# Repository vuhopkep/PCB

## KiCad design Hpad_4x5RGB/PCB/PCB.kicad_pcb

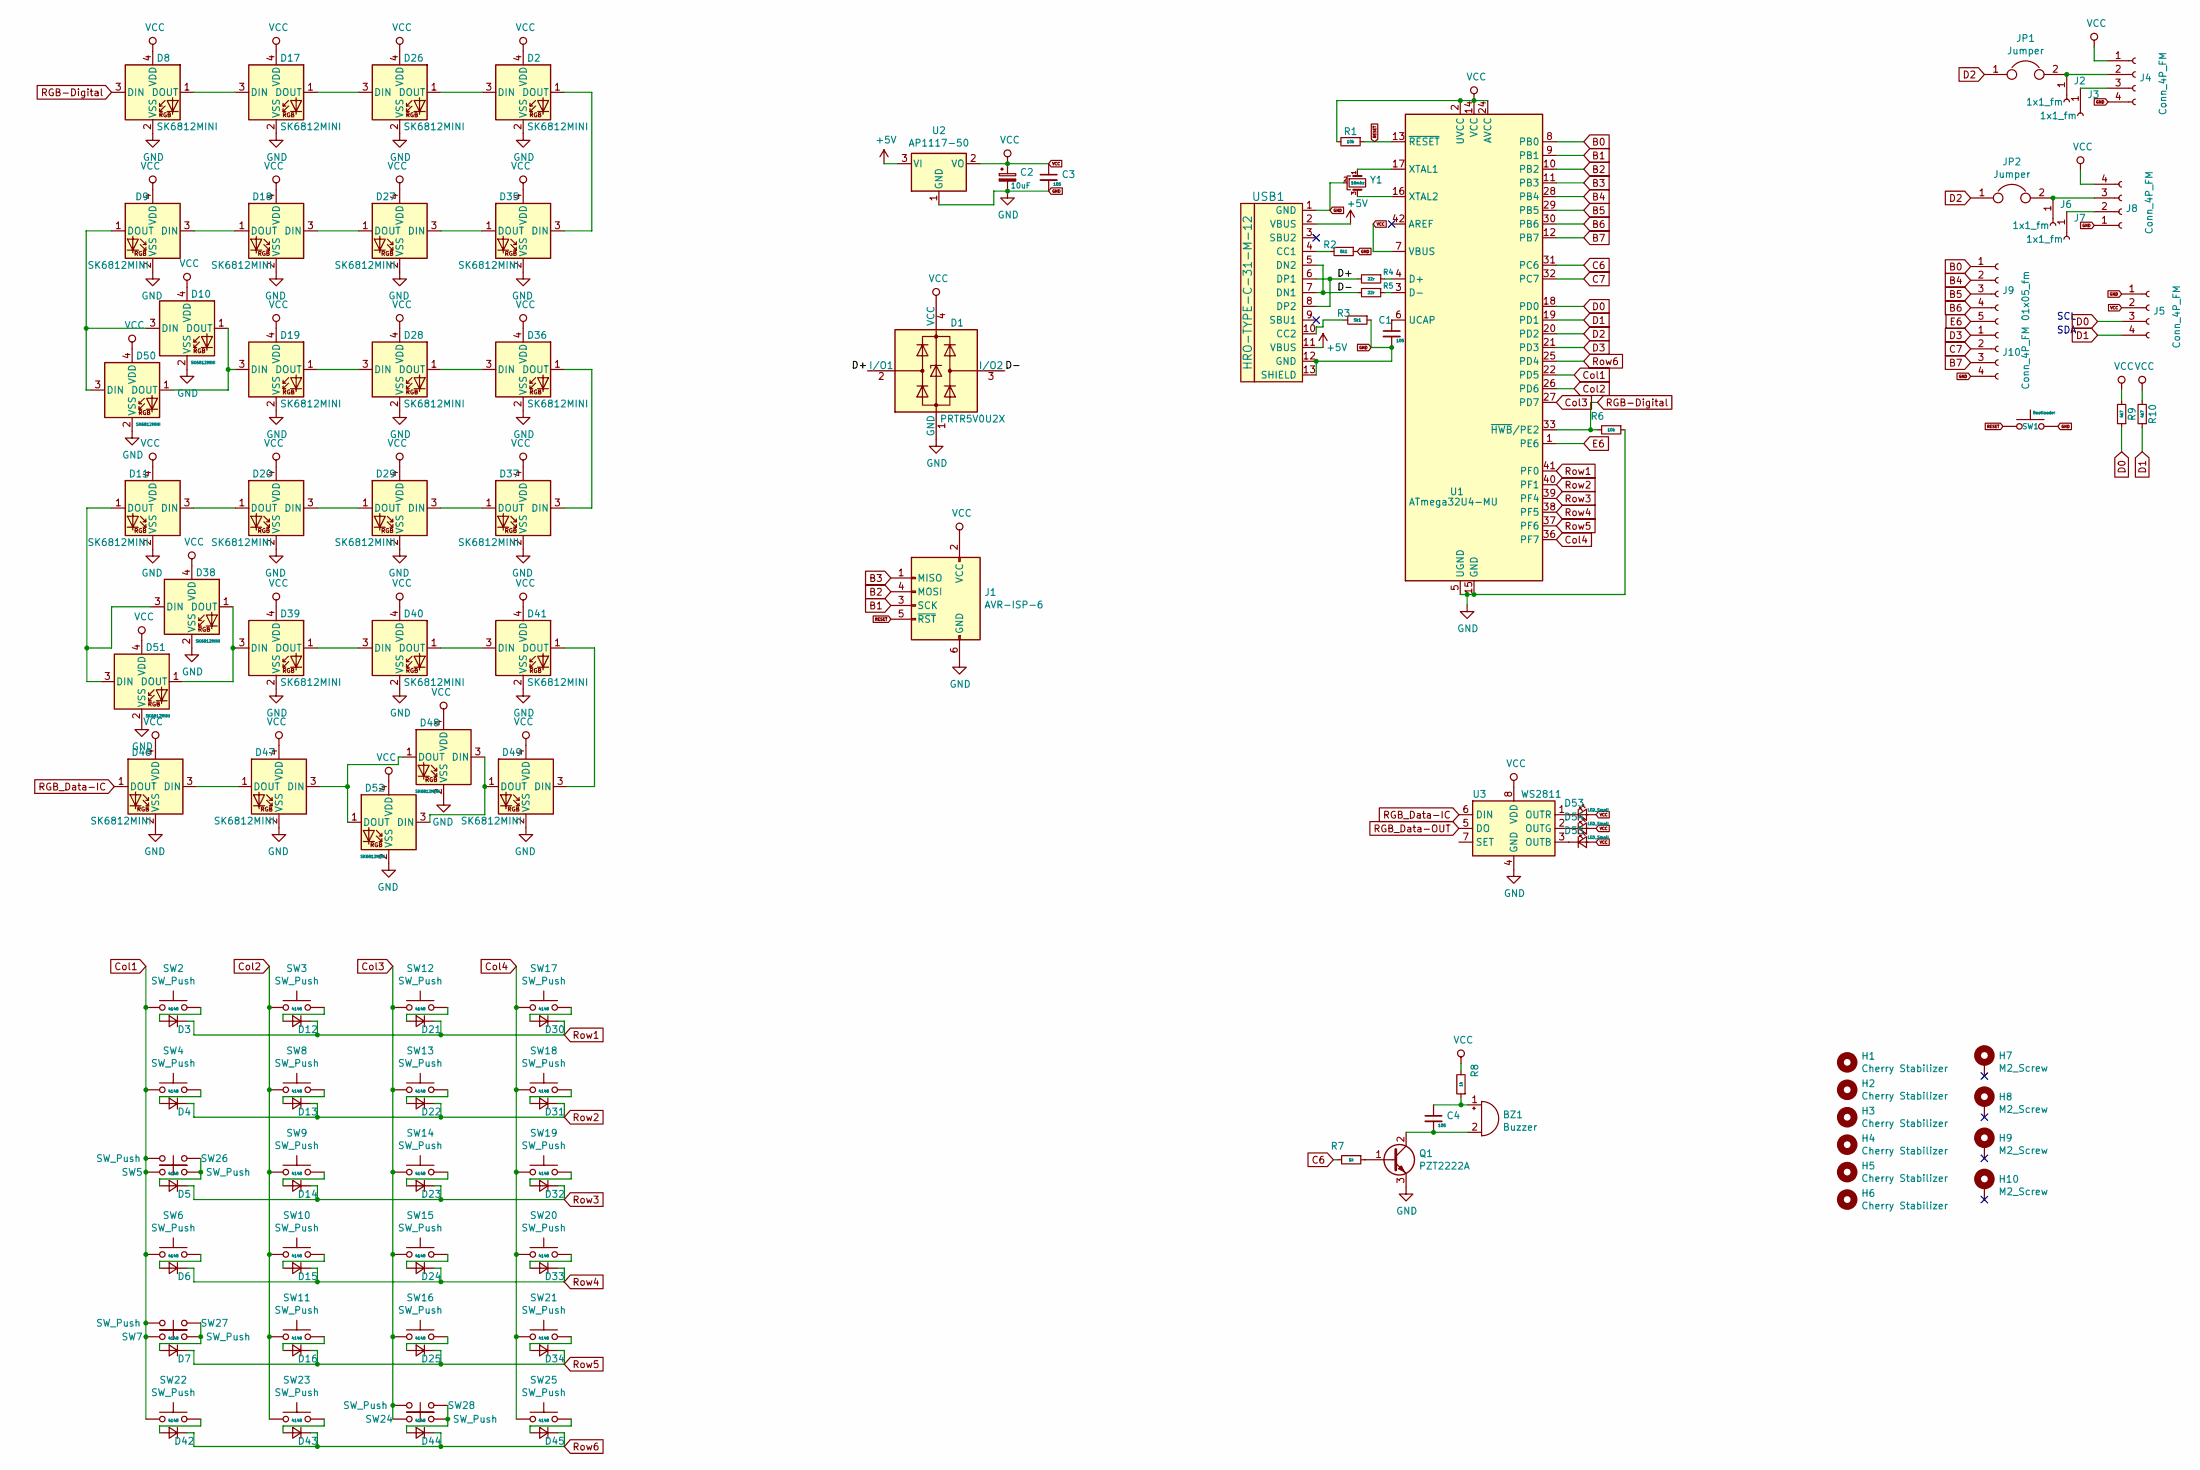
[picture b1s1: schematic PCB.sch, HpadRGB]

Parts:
BZ1: Buzzer; Buzzer_Murata_PKMCS0909E4000-R1
C1, C3, C4: 105; C_0805
C2: 10uF; CP_Tantalum_3216
D1: PRTR5V0U2X; SOT-143
D2, D8, D9, D10, D11, D17, D18, D19, D20, D26, D27, D28, D29, D35, D36, D37, D38, D39, D40, D41, D46, D47, D48, D49, D50, D51, D52: SK6812MINI; LED_SK6812-3535_Backlight
D3, D4, D5, D6, D7, D12, D13, D14, D15, D16, D21, D22, D23, D24, D25, D30, D31, D32, D33, D34, D42, D43, D44, D45: 4148; D_SOD-323_HandSoldering
D53, D54, D55: LED_Small; LED_0805_2012Metric
H1, H2, H3, H4, H5, H6: Cherry Stabilizer; Cherry_Stab_PCBMounted
H7, H8, H9, H10: M2_Screw; MountingHole_2.2mm_M2_Pad_Via
J1: AVR-ISP-6; AVR_ISP_6
J2, J3, J6, J7: 1x1_fm; PinHeader_1x01_P1.00mm_Vertical
J4, J8: Conn_4P_FM; HTP-CON-M411P
J5, J10: Conn_4P_FM; PinHeader_1x04_P2.54mm_Vertical
J9: 01x05_fm; PinSocket_1x05_P2.54mm_Vertical
JP1, JP2: Jumper; SolderJumper-2_P1.3mm_Open_RoundedPad1.0x1.5mm
Q1: PZT2222A; SOT-23W
R1, R6: 10k; R_0805_2012Metric
R2, R3: 5k1; R_0805_2012Metric
R4, R5: 22r; R_0805_2012Metric
R7, R8: 1k; R_0805_2012Metric
R9, R10: 4k7; R_0805_2012Metric
SW1: Bootloader; SW_SPST_B3U-1000P-B
SW2, SW3, SW4, SW5, SW6, SW7, SW8, SW9, SW10, SW11, SW12, SW13, SW14, SW15, SW16, SW17, SW18, SW19, SW20, SW21, SW22, SW23, SW24, SW25, SW26, SW27, SW28: SW_Push; CHERRY&ALPS_PCB_100H
U1: ATmega32U4-MU; QFN-44-1EP_7x7mm_P0.5mm_EP5.2x5.2mm
U2: AP1117-50; SOT-223-3_TabPin2
U3: WS2811; SOIC-8_3.9x4.9mm_P1.27mm
USB1: HRO-TYPE-C-31-M-12
Y1: 16mhz; Resonator_SMD_muRata_CSTxExxV-3Pin_3.0x1.1mm

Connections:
+5V: U2.3 (VI), USB1.2 (VBUS), USB1.11 (VBUS)
/D+: D1.2 (I/O1), R4.2, USB1.6 (DP1), USB1.8 (DP2)
/D-: D1.3 (I/O2), R5.2, USB1.5 (DN2), USB1.7 (DN1)
B0: J9.1, U1.8 (PB0)
B1: J1.3 (SCK), U1.9 (PB1)
B2: J1.4 (MOSI), U1.10 (PB2)
B3: J1.1 (MISO), U1.11 (PB3)
B4: J9.2, U1.28 (PB4)
B5: J9.3, U1.29 (PB5)
B6: J9.4, U1.30 (PB6)
B7: J10.3, U1.12 (PB7)
C6: R7.2, U1.31 (PC6)
C7: J10.2, U1.32 (PC7)
Col1: SW2.1, SW4.1, SW5.1, SW6.1, SW7.1, SW22.1, SW26.2, SW27.2, U1.22 (PD5)
Col2: SW3.1, SW8.1, SW9.1, SW10.1, SW11.1, SW23.1, U1.26 (PD6)
Col3: SW12.1, SW13.1, SW14.1, SW15.1, SW16.1, SW24.1, SW28.2, U1.27 (PD7)
Col4: SW17.1, SW18.1, SW19.1, SW20.1, SW21.1, SW25.1, U1.36 (PF7)
D0: J5.3, R9.1, U1.18 (PD0)
D1: J5.4, R10.1, U1.19 (PD1)
D2: JP1.1, JP2.1, U1.20 (PD2)
D3: J10.1, U1.21 (PD3)
E6: J9.5, U1.1 (PE6)
GND: C1.2, C2.2, C3.2, D1.1 (GND), D2.2 (VSS), D8.2 (VSS), D9.2 (VSS), D10.2 (VSS), D11.2 (VSS), D17.2 (VSS), D18.2 (VSS), D19.2 (VSS), D20.2 (VSS), D26.2 (VSS), D27.2 (VSS), D28.2 (VSS), D29.2 (VSS), D35.2 (VSS), D36.2 (VSS), D37.2 (VSS), D38.2 (VSS), D39.2 (VSS), D40.2 (VSS), D41.2 (VSS), D46.2 (VSS), D47.2 (VSS), D48.2 (VSS), D49.2 (VSS), D50.2 (VSS), D51.2 (VSS), D52.2 (VSS), J1.6 (GND), J4.4, J5.1, J8.1, J10.4, Q1.3 (E), R2.1, R3.1, R6.1, SW1.2, U1.5 (UGND), U1.15 (GND), U1.23 (GND), U1.35 (GND), U1.43 (GND), U1.45 (GND), U2.1 (GND), U3.4 (GND), USB1.1 (GND), USB1.12 (GND), USB1.13 (SHIELD), Y1.2; also elsewhere on the board
unnamed: BZ1.1 (-), C4.1, R8.1
unnamed: BZ1.2 (+), C4.2, Q1.2 (C)
unnamed: C1.1, U1.6 (UCAP)
unnamed: D2.1 (DOUT), D35.3 (DIN)
unnamed: D2.3 (DIN), D26.1 (DOUT)
unnamed: D3.2 (A), SW2.2
unnamed: D4.2 (A), SW4.2
unnamed: D5.2 (A), SW5.2, SW26.1
unnamed: D6.2 (A), SW6.2
unnamed: D7.2 (A), SW7.2, SW27.1
unnamed: D10.1 (DOUT), D19.3 (DIN), D50.1 (DOUT)
unnamed: D9.1 (DOUT), D10.3 (DIN), D50.3 (DIN)
unnamed: D11.1 (DOUT), D38.3 (DIN), D51.3 (DIN)
unnamed: D11.3 (DIN), D20.1 (DOUT)
unnamed: D12.2 (A), SW3.2
unnamed: D13.2 (A), SW8.2
unnamed: D14.2 (A), SW9.2
unnamed: D15.2 (A), SW10.2
unnamed: D16.2 (A), SW11.2
unnamed: D17.1 (DOUT), D26.3 (DIN)
unnamed: D8.1 (DOUT), D17.3 (DIN)
unnamed: D9.3 (DIN), D18.1 (DOUT)
unnamed: D18.3 (DIN), D27.1 (DOUT)
unnamed: D19.1 (DOUT), D28.3 (DIN)
unnamed: D20.3 (DIN), D29.1 (DOUT)
unnamed: D21.2 (A), SW12.2
unnamed: D22.2 (A), SW13.2
unnamed: D23.2 (A), SW14.2
unnamed: D24.2 (A), SW15.2
unnamed: D25.2 (A), SW16.2
unnamed: D27.3 (DIN), D35.1 (DOUT)
unnamed: D28.1 (DOUT), D36.3 (DIN)
unnamed: D29.3 (DIN), D37.1 (DOUT)
unnamed: D30.2 (A), SW17.2
unnamed: D31.2 (A), SW18.2
unnamed: D32.2 (A), SW19.2
unnamed: D33.2 (A), SW20.2
unnamed: D34.2 (A), SW21.2
unnamed: D36.1 (DOUT), D37.3 (DIN)
unnamed: D38.1 (DOUT), D39.3 (DIN), D51.1 (DOUT)
unnamed: D39.1 (DOUT), D40.3 (DIN)
unnamed: D40.1 (DOUT), D41.3 (DIN)
unnamed: D41.1 (DOUT), D49.3 (DIN)
unnamed: D42.2 (A), SW22.2
unnamed: D43.2 (A), SW23.2
unnamed: D44.2 (A), SW24.2, SW28.1
unnamed: D45.2 (A), SW25.2
unnamed: D46.3 (DIN), D47.1 (DOUT)
unnamed: D47.3 (DIN), D48.1 (DOUT), D52.1 (DOUT)
unnamed: D48.3 (DIN), D49.1 (DOUT), D52.3 (DIN)
unnamed: D53.1 (K), U3.1 (OUTR)
unnamed: D54.1 (K), U3.2 (OUTG)
unnamed: D55.1 (K), U3.3 (OUTB)
unnamed: J2.1, J4.2, JP1.2
unnamed: J3.1, J4.3
unnamed: J6.1, J8.3, JP2.2
unnamed: J7.1, J8.2
unnamed: Q1.1 (B), R7.1
unnamed: R2.2, USB1.4 (CC1)
unnamed: R3.2, USB1.10 (CC2)
unnamed: R4.1, U1.4 (D+)
unnamed: R5.1, U1.3 (D-)
unnamed: U1.16 (XTAL2), Y1.3
unnamed: U1.17 (XTAL1), Y1.1
RESET: J1.5 (~RST), R1.1, SW1.1, U1.13 (~RESET); also elsewhere on the board
RGB-Digital: D8.3 (DIN), R6.2, U1.33 (~HWB~/PE2)
RGB_Data-IC: D46.1 (DOUT), U3.6 (DIN)
RGB_Data-OUT: U3.5 (DO)
Row1: D3.1 (K), D12.1 (K), D21.1 (K), D30.1 (K), U1.41 (PF0)
Row2: D4.1 (K), D13.1 (K), D22.1 (K), D31.1 (K), U1.40 (PF1)
Row3: D5.1 (K), D14.1 (K), D23.1 (K), D32.1 (K), U1.39 (PF4)
Row4: D6.1 (K), D15.1 (K), D24.1 (K), D33.1 (K), U1.38 (PF5)
Row5: D7.1 (K), D16.1 (K), D25.1 (K), D34.1 (K), U1.37 (PF6)
Row6: D42.1 (K), D43.1 (K), D44.1 (K), D45.1 (K), U1.25 (PD4)
VCC: C2.1, C3.1, D1.4 (VCC), D2.4 (VDD), D8.4 (VDD), D9.4 (VDD), D10.4 (VDD), D11.4 (VDD), D17.4 (VDD), D18.4 (VDD), D19.4 (VDD), D20.4 (VDD), D26.4 (VDD), D27.4 (VDD), D28.4 (VDD), D29.4 (VDD), D35.4 (VDD), D36.4 (VDD), D37.4 (VDD), D38.4 (VDD), D39.4 (VDD), D40.4 (VDD), D41.4 (VDD), D46.4 (VDD), D47.4 (VDD), D48.4 (VDD), D49.4 (VDD), D50.4 (VDD), D51.4 (VDD), D52.4 (VDD), D53.2 (A), D54.2 (A), D55.2 (A), J1.2 (VCC), J4.1, J5.2, J8.4, R1.2, R8.2, R9.2, R10.2, U1.2 (UVCC), U1.7 (VBUS), U1.14 (VCC), U1.24 (AVCC), U1.34 (VCC), U1.44 (AVCC), U2.2 (VO), U3.8 (VDD)

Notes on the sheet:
SCL
SDA

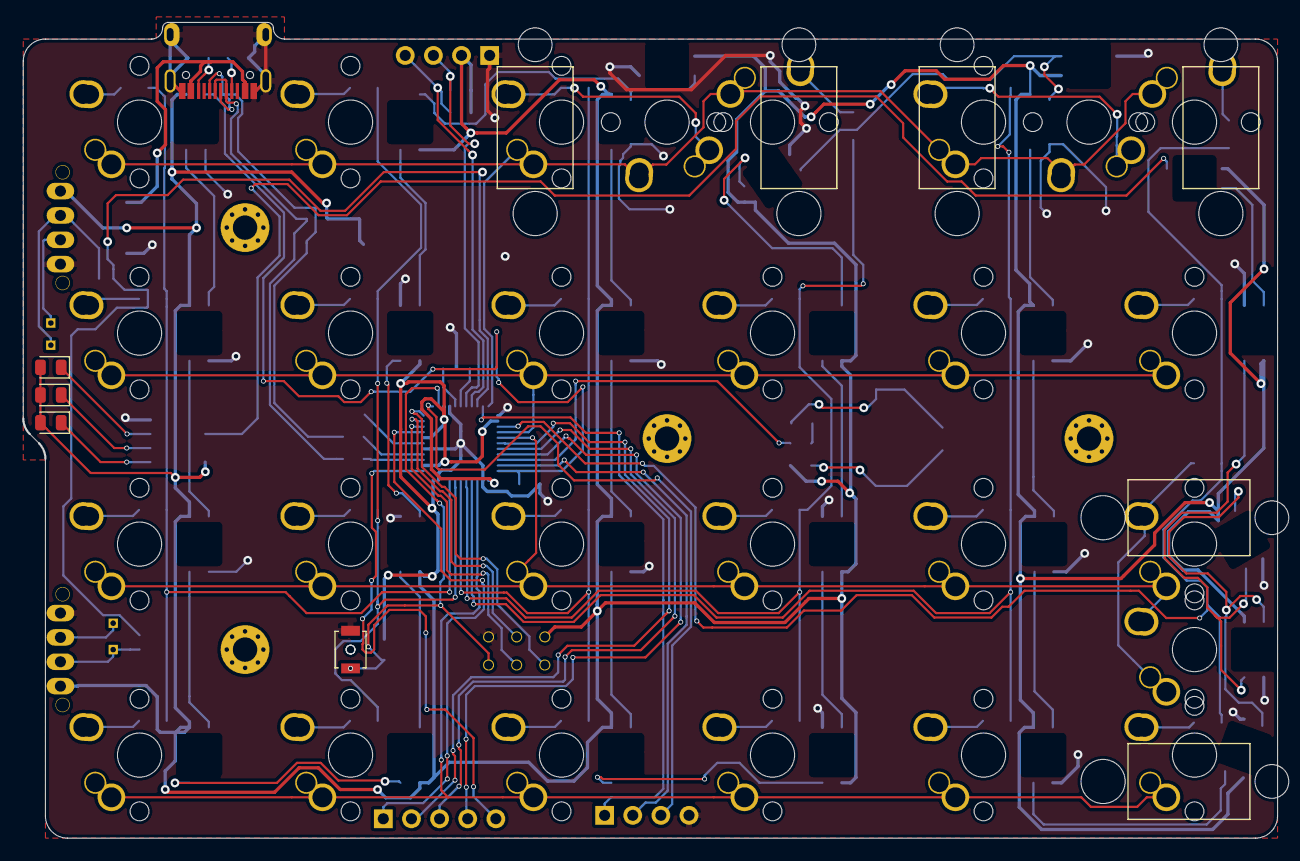
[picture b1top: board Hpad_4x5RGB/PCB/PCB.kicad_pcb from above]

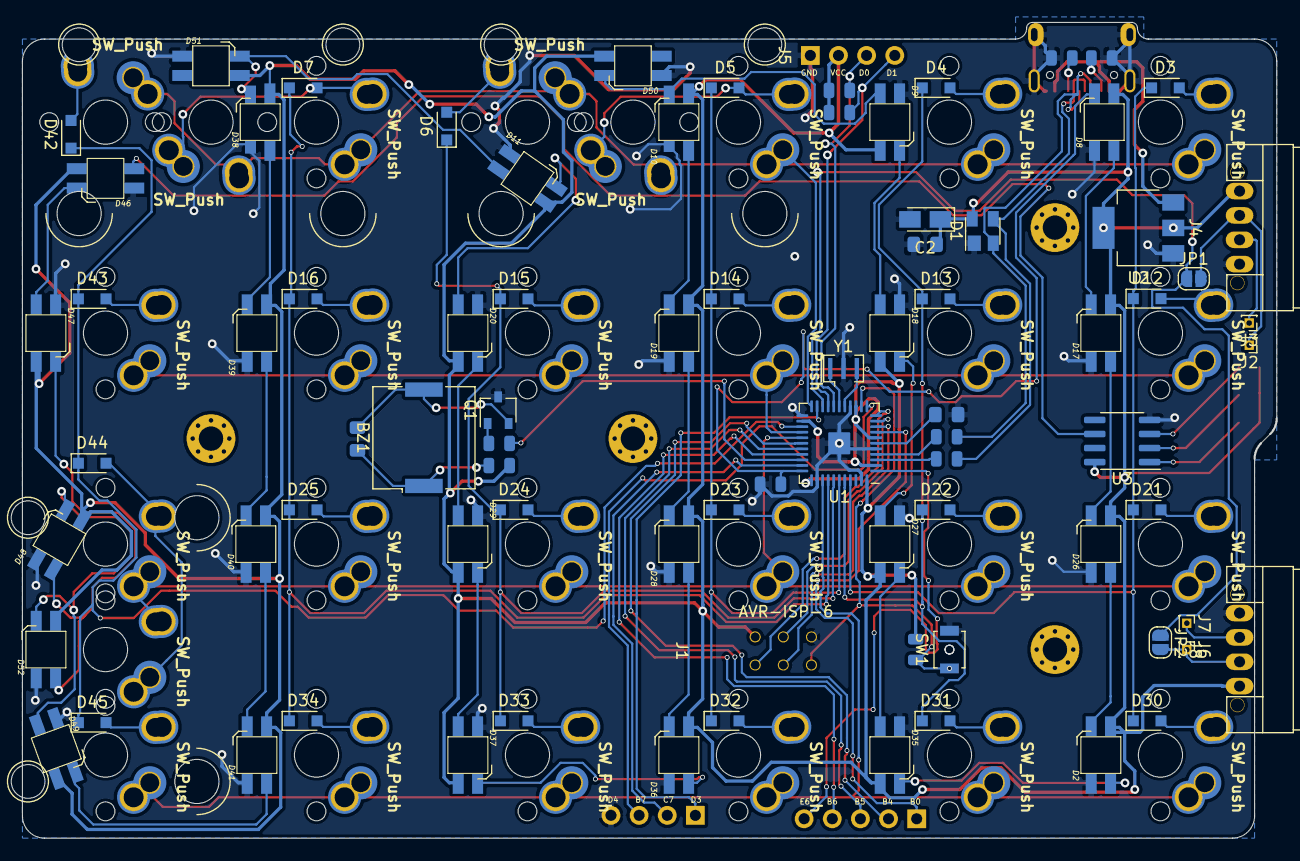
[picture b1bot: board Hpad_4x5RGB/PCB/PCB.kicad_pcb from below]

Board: 2 copper layers, 113.2 x 73.7 mm, 127 parts (83 on the bottom side), 97 nets.

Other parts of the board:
SW1#2: Bootloader; SW_SPST_B3U-1000P-B

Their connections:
GND: SW1#2.2; also elsewhere on the board
RESET: SW1#2.1; also elsewhere on the board

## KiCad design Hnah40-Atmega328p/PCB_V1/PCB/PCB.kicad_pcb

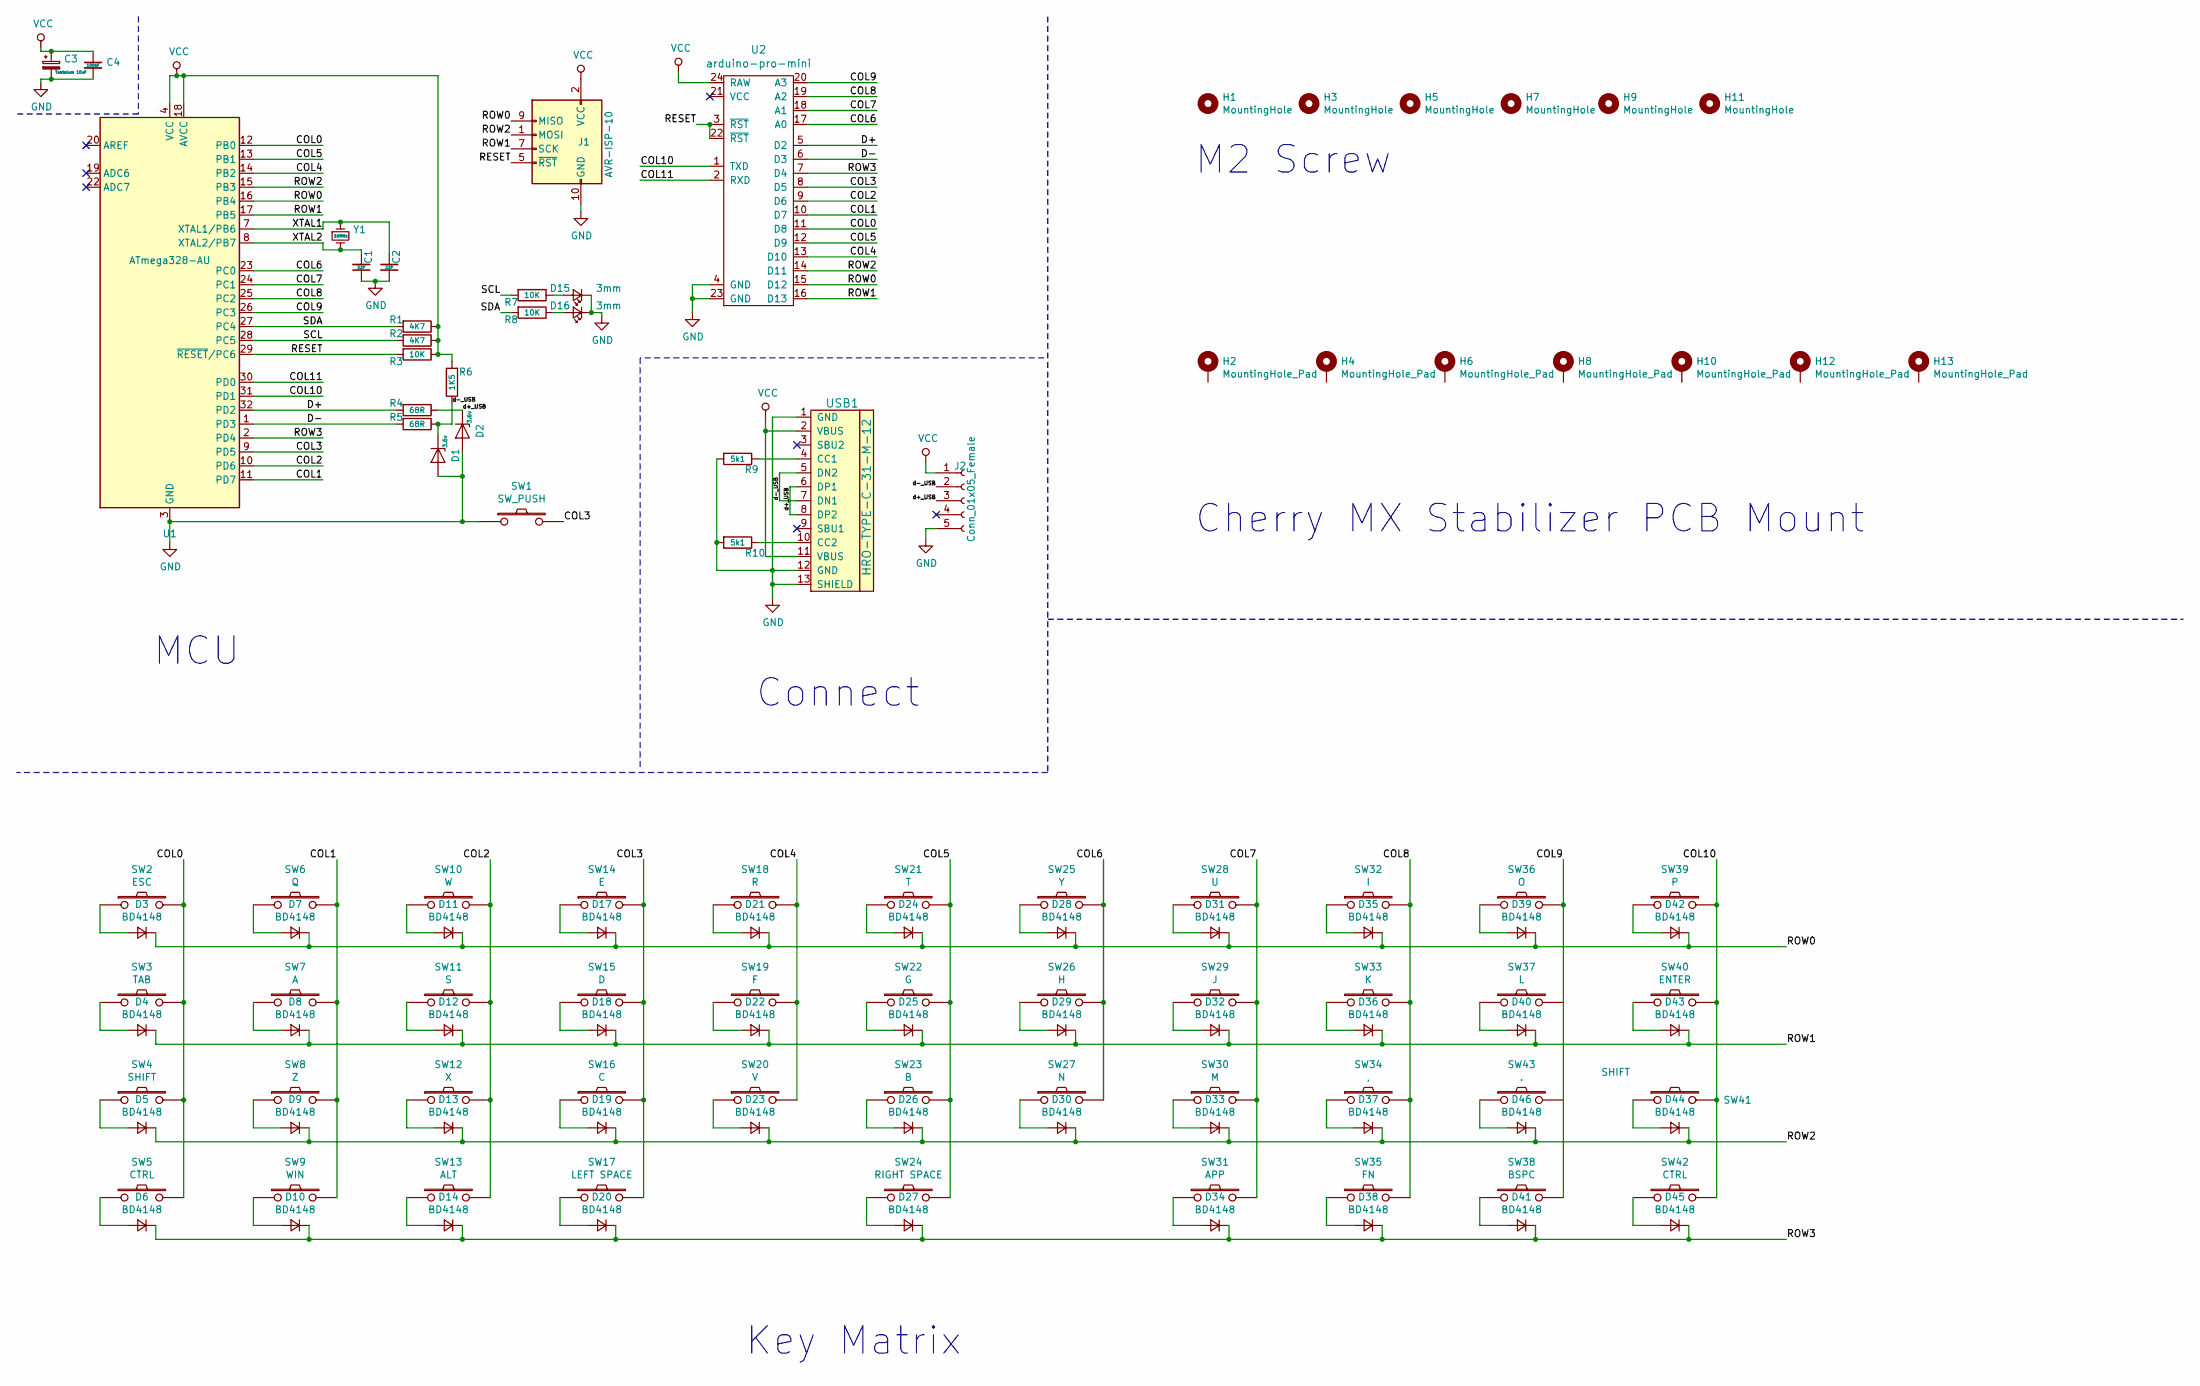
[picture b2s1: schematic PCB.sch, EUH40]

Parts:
C1, C2: 22P; C_0805_2012Metric
C3: Tantalum 10uF; CP_Tantalum_3216
C4: 100nF; C_0805_2012Metric
D1, D2: 3.6v; D_SOD-123
D3, D4, D5, D6, D7, D8, D9, D10, D11, D12, D13, D14, D17, D18, D19, D20, D21, D22, D23, D24, D25, D26, D27, D28, D29, D30, D31, D32, D33, D34, D35, D36, D37, D38, D39, D40, D41, D42, D43, D44, D45, D46: BD4148; D_0805_Mab_ideal
D15, D16: 3mm
H1, H3, H5, H7, H9, H11: MountingHole; Cherry_Stab_PCBMounted
H2, H4, H6, H8, H10, H12, H13: MountingHole_Pad; Poker_oval_hole
J1: AVR-ISP-10; AVR_ICSP_5x2
J2: Conn_01x05_Female; PinHeader_1x05_P2.54mm_Vertical
R1, R2: 4K7; R_0805_2012Metric
R3, R7, R8: 10K; R_0805_2012Metric
R4, R5: 68R; R_0805_2012Metric
R6: 1K5; R_0805_2012Metric
R9, R10: 5k1; R_0805_2012Metric
SW1: SW_PUSH; Nidec_Copal_SH-7010A
SW2: ESC; CHERRY_PCB_100H
SW3: TAB; CHERRY_PCB_100H
SW4: SHIFT; CHERRY_PCB_100H
SW5, SW42: CTRL; CHERRY_PCB_100H
SW6: Q; CHERRY_PCB_100H
SW7: A; CHERRY_PCB_100H
SW8: Z; CHERRY_PCB_100H
SW9: WIN; CHERRY_PCB_100H
SW10: W; CHERRY_PCB_100H
SW11: S; CHERRY_PCB_100H
SW12: X; CHERRY_PCB_100H
SW13: ALT; CHERRY_PCB_100H
SW14: E; CHERRY_PCB_100H
SW15: D; CHERRY_PCB_100H
SW16: C; CHERRY_PCB_100H
SW17: LEFT SPACE; CHERRY_PCB_100H
SW18: R; CHERRY_PCB_100H
SW19: F; CHERRY_PCB_100H
SW20: V; CHERRY_PCB_100H
SW21: T; CHERRY_PCB_100H
SW22: G; CHERRY_PCB_100H
SW23: B; CHERRY_PCB_100H
SW24: RIGHT SPACE; CHERRY_PCB_100H
SW25: Y; CHERRY_PCB_100H
SW26: H; CHERRY_PCB_100H
SW27: N; CHERRY_PCB_100H
SW28: U; CHERRY_PCB_100H
SW29: J; CHERRY_PCB_100H
SW30: M; CHERRY_PCB_100H
SW31: APP; CHERRY_PCB_100H
SW32: I; CHERRY_PCB_100H
SW33: K; CHERRY_PCB_100H
SW34: ,; CHERRY_PCB_100H
SW35: FN; CHERRY_PCB_100H
SW36: O; CHERRY_PCB_100H
SW37: L; CHERRY_PCB_100H
SW38: BSPC; CHERRY_PCB_100H
SW39: P; CHERRY_PCB_100H
SW40: ENTER; CHERRY_PCB_100H
SW41: SHIFT; CherryMX_Shift
SW43: .; CHERRY_PCB_100H
U1: ATmega328-AU; TQFP-32_7x7mm_P0.8mm
U2: arduino-pro-mini; Pro_mini
USB1: HRO-TYPE-C-31-M-12
Y1: 16MHz; Crystal_SMD_5032

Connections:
/COL0: SW2.2, SW3.2, SW4.2, SW5.2, U1.12 (PB0), U2.11 (D8)
/COL1: SW6.2, SW7.2, SW8.2, SW9.2, U1.11 (PD7), U2.10 (D7)
/COL2: SW10.2, SW11.2, SW12.2, SW13.2, U1.10 (PD6), U2.9 (D6)
/COL3: SW1.2, SW14.2, SW15.2, SW16.2, SW17.2, U1.9 (PD5), U2.8 (D5)
/COL4: SW18.2, SW19.2, SW20.2, U1.14 (PB2), U2.13 (D10)
/COL5: SW21.2, SW22.2, SW23.2, SW24.2, U1.13 (PB1), U2.12 (D9)
/COL6: SW25.2, SW26.2, SW27.2, U1.23 (PC0), U2.17 (A0)
/COL7: SW28.2, SW29.2, SW30.2, SW31.2, U1.24 (PC1), U2.18 (A1)
/COL8: SW32.2, SW33.2, SW34.2, SW35.2, U1.25 (PC2), U2.19 (A2)
/COL9: SW36.2, SW37.2, SW38.2, SW43.2, U1.26 (PC3), U2.20 (A3)
/COL10: SW39.2, SW40.2, SW41.2, SW42.2, U1.31 (PD1), U2.1 (TXD)
/COL11: U1.30 (PD0), U2.2 (RXD)
/D+: R4.2, U1.32 (PD2), U2.5 (D2)
/D-: R5.2, U1.1 (PD3), U2.6 (D3)
/RESET: J1.5 (~RST), R3.2, U1.29 (~RESET~/PC6), U2.3 (~RST), U2.22 (~RST)
/ROW0: D3.1 (K), D7.1 (K), D11.1 (K), D17.1 (K), D21.1 (K), D24.1 (K), D28.1 (K), D31.1 (K), D35.1 (K), D39.1 (K), D42.1 (K), J1.9 (MISO), U1.16 (PB4), U2.15 (D12)
/ROW1: D4.1 (K), D8.1 (K), D12.1 (K), D18.1 (K), D22.1 (K), D25.1 (K), D29.1 (K), D32.1 (K), D36.1 (K), D40.1 (K), D43.1 (K), J1.7 (SCK), U1.17 (PB5), U2.16 (D13)
/ROW2: D5.1 (K), D9.1 (K), D13.1 (K), D19.1 (K), D23.1 (K), D26.1 (K), D30.1 (K), D33.1 (K), D37.1 (K), D44.1 (K), D46.1 (K), J1.1 (MOSI), U1.15 (PB3), U2.14 (D11)
/ROW3: D6.1 (K), D10.1 (K), D14.1 (K), D20.1 (K), D27.1 (K), D34.1 (K), D38.1 (K), D41.1 (K), D45.1 (K), U1.2 (PD4), U2.7 (D4)
/SCL: R2.2, R7.2, U1.28 (PC5)
/SDA: R1.2, R8.2, U1.27 (PC4)
/XTAL1: C2.2, U1.7 (XTAL1/PB6), Y1.1
/XTAL2: C1.2, U1.8 (XTAL2/PB7), Y1.2
/d+_USB: D2.1 (K), J2.3, R4.1, USB1.6 (DP1), USB1.8 (DP2)
/d-_USB: D1.1 (K), J2.2, R5.1, R6.1, USB1.5 (DN2), USB1.7 (DN1)
GND: C1.1, C2.1, C3.2, C4.2, D1.2 (A), D2.2 (A), D15.1 (K), D16.1 (K), J1.4 (GND), J1.6 (GND), J1.8 (GND), J1.10 (GND), J2.5, R9.2, R10.2, SW1.1, U1.3 (GND), U1.5 (GND), U1.21 (GND), U2.4 (GND), U2.23 (GND), USB1.1 (GND), USB1.12 (GND), USB1.13 (SHIELD)
unnamed: D3.2 (A), SW2.1
unnamed: D4.2 (A), SW3.1
unnamed: D5.2 (A), SW4.1
unnamed: D6.2 (A), SW5.1
unnamed: D7.2 (A), SW6.1
unnamed: D8.2 (A), SW7.1
unnamed: D9.2 (A), SW8.1
unnamed: D10.2 (A), SW9.1
unnamed: D11.2 (A), SW10.1
unnamed: D12.2 (A), SW11.1
unnamed: D13.2 (A), SW12.1
unnamed: D14.2 (A), SW13.1
unnamed: D15.2 (A), R7.1
unnamed: D16.2 (A), R8.1
unnamed: D17.2 (A), SW14.1
unnamed: D18.2 (A), SW15.1
unnamed: D19.2 (A), SW16.1
unnamed: D20.2 (A), SW17.1
unnamed: D21.2 (A), SW18.1
unnamed: D22.2 (A), SW19.1
unnamed: D23.2 (A), SW20.1
unnamed: D24.2 (A), SW21.1
unnamed: D25.2 (A), SW22.1
unnamed: D26.2 (A), SW23.1
unnamed: D27.2 (A), SW24.1
unnamed: D28.2 (A), SW25.1
unnamed: D29.2 (A), SW26.1
unnamed: D30.2 (A), SW27.1
unnamed: D31.2 (A), SW28.1
unnamed: D32.2 (A), SW29.1
unnamed: D33.2 (A), SW30.1
unnamed: D34.2 (A), SW31.1
unnamed: D35.2 (A), SW32.1
unnamed: D36.2 (A), SW33.1
unnamed: D37.2 (A), SW34.1
unnamed: D38.2 (A), SW35.1
unnamed: D39.2 (A), SW36.1
unnamed: D40.2 (A), SW37.1
unnamed: D41.2 (A), SW38.1
unnamed: D42.2 (A), SW39.1
unnamed: D43.2 (A), SW40.1
unnamed: D44.2 (A), SW41.1
unnamed: D45.2 (A), SW42.1
unnamed: D46.2 (A), SW43.1
unnamed: R9.1, USB1.4 (CC1)
unnamed: R10.1, USB1.10 (CC2)
VCC: C3.1, C4.1, J1.2 (VCC), J2.1, R1.1, R2.1, R3.1, R6.2, U1.4 (VCC), U1.6 (VCC), U1.18 (AVCC), U2.24 (RAW), USB1.2 (VBUS), USB1.11 (VBUS)

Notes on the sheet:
M2 Screw
Cherry MX Stabilizer PCB Mount
MCU
Connect
Key Matrix

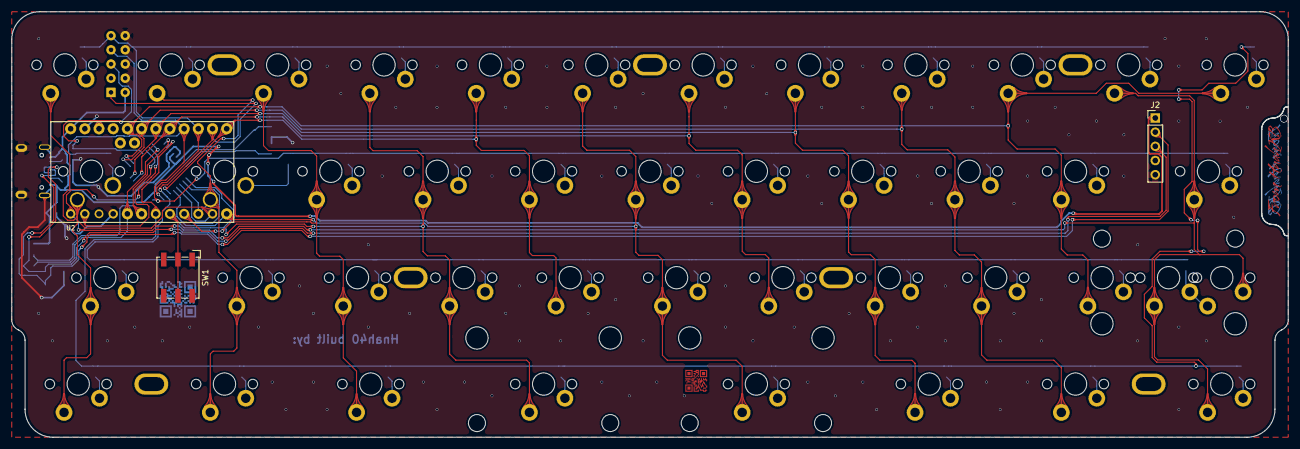
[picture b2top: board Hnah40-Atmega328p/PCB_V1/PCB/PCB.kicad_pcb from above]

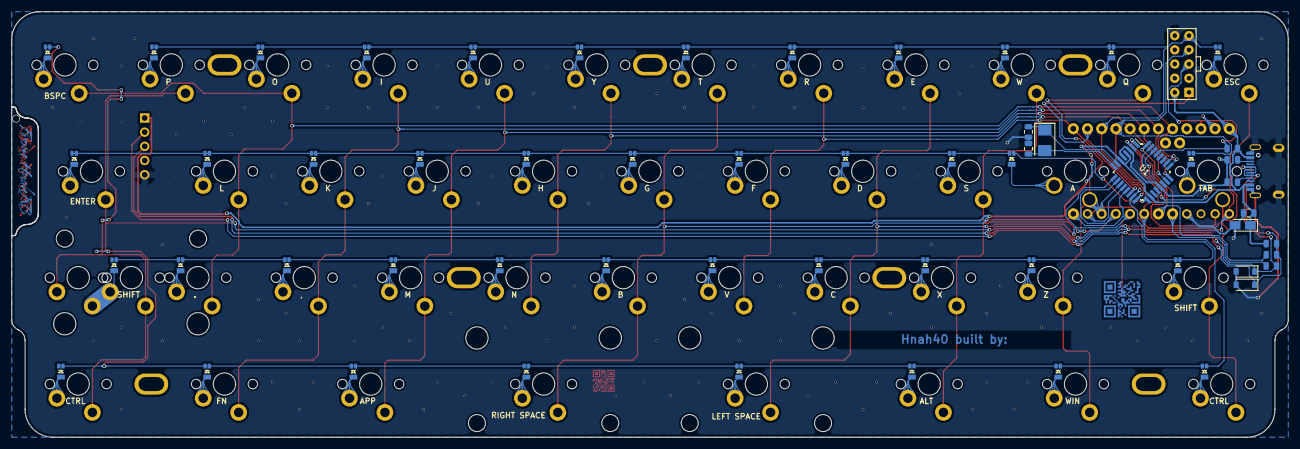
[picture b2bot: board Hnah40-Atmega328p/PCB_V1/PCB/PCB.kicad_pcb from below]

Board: 2 copper layers, 228.6 x 76.2 mm, 116 parts (58 on the bottom side), 69 nets.

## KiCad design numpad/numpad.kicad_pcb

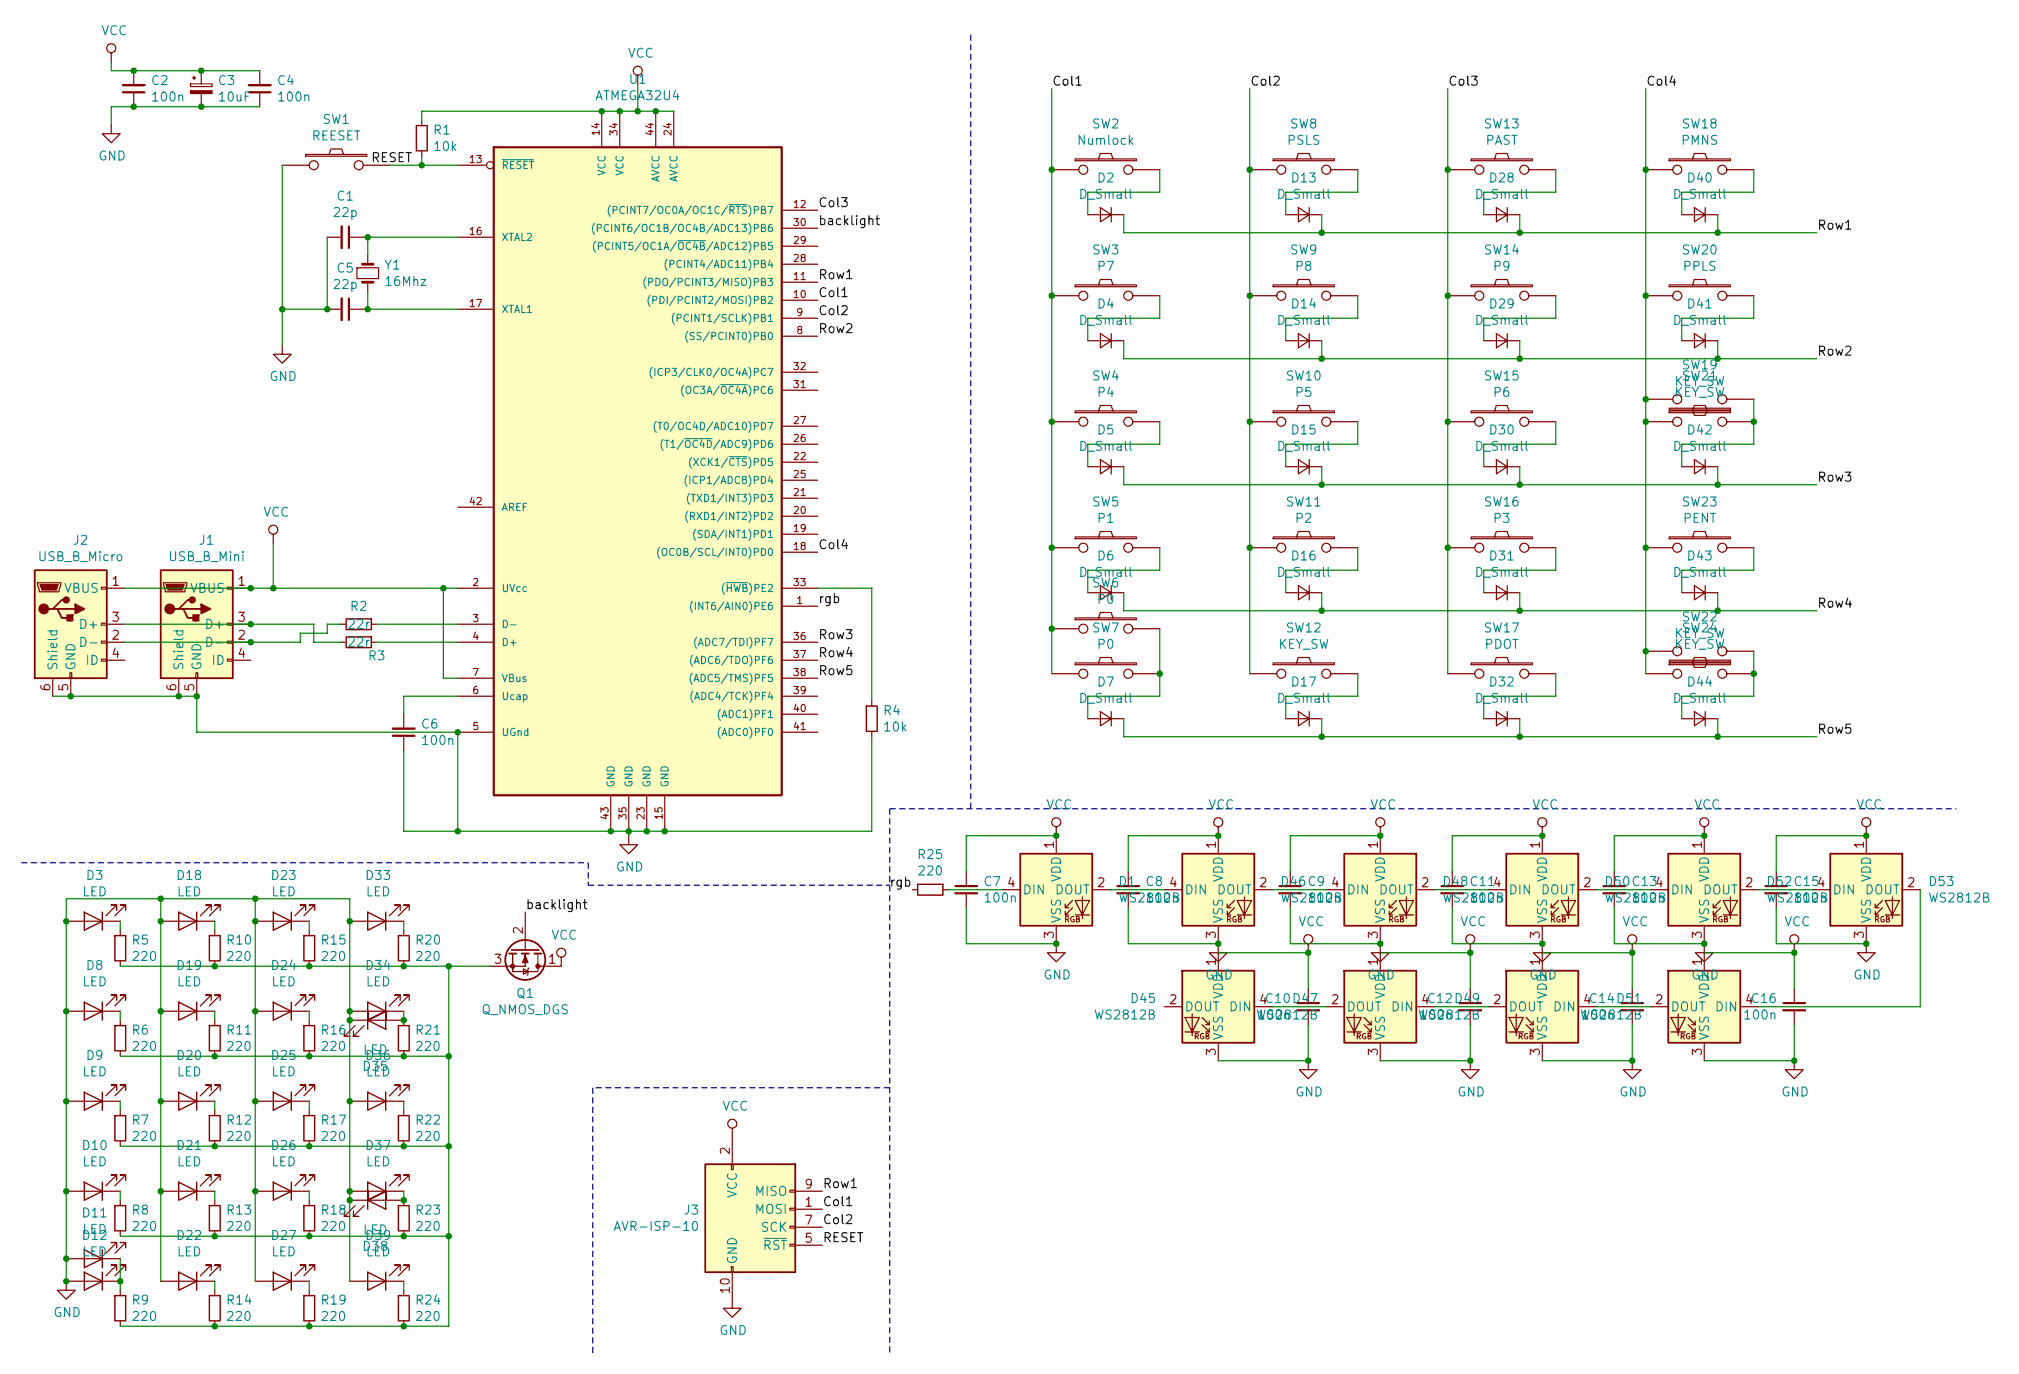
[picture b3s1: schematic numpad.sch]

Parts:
C1, C5: 22p; C_0805
C2, C4, C6, C7, C8, C9, C10, C11, C12, C13, C14, C15, C16: 100n; C_0805
C3: 10uF; CP_Tantalum_3216
D1, D45, D46, D47, D48, D49, D50, D51, D52, D53: WS2812B; LED_WS2812B_PLCC4_5.0x5.0mm_P3.2mm
D2, D4, D5, D6, D7, D13, D14, D15, D16, D17, D28, D29, D30, D31, D32, D40, D41, D42, D43, D44: D_Small; D_0805
D3, D8, D9, D10, D11, D12, D18, D19, D20, D21, D22, D23, D24, D25, D26, D27, D33, D34, D35, D36, D37, D38, D39: LED; CHERRY_MX_LED_3MM
J1: USB_B_Mini; USB_MINI_MAB
J2: USB_B_Micro; USB_Micro
J3: AVR-ISP-10; AVR_ICSP_5x2
Q1: Q_NMOS_DGS; SOT-23
R1, R4: 10k; R_0805
R2, R3: 22r; R_0805
R5, R6, R7, R8, R9, R10, R11, R12, R13, R14, R15, R16, R17, R18, R19, R20, R21, R22, R23, R24, R25: 220; R_0805
SW1: REESET; SW_SPST_TL3342
SW2: Numlock; CHERRY_PCB_100H
SW3: P7; CHERRY_PCB_100H
SW4: P4; CHERRY_PCB_100H
SW5: P1; CHERRY_PCB_100H
SW6, SW7: P0; CHERRY_PCB_100H
SW8: PSLS; CHERRY_PCB_100H
SW9: P8; CHERRY_PCB_100H
SW10: P5; CHERRY_PCB_100H
SW11: P2; CHERRY_PCB_100H
SW12, SW19, SW21, SW22, SW24: KEY_SW; CHERRY_PCB_100H
SW13: PAST; CHERRY_PCB_100H
SW14: P9; CHERRY_PCB_100H
SW15: P6; CHERRY_PCB_100H
SW16: P3; CHERRY_PCB_100H
SW17: PDOT; CHERRY_PCB_100H
SW18: PMNS; CHERRY_PCB_100H
SW20: PPLS; CHERRY_PCB_100H
SW23: PENT; CHERRY_PCB_100H
U1: ATMEGA32U4; TQFP-44_Pitch0.8mm
Y1: 16Mhz; Crystal_SMD_5032

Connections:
/Col1: J3.1 (MOSI), SW2.1, SW3.1, SW4.1, SW5.1, SW6.1, SW7.1, U1.10 ((PDI/PCINT2/MOSI)PB2)
/Col2: J3.7 (SCK), SW8.1, SW9.1, SW10.1, SW11.1, SW12.1, U1.9 ((PCINT1/SCLK)PB1)
/Col3: SW13.1, SW14.1, SW15.1, SW16.1, SW17.1, U1.12 ((PCINT7/OC0A/OC1C/~RTS~)PB7)
/Col4: SW18.1, SW19.2, SW20.1, SW21.1, SW22.2, SW23.1, SW24.1, U1.18 ((OC0B/SCL/INT0)PD0)
/RESET: J3.5 (~RST), R1.2, SW1.2, U1.13 (~RESET~)
/Row1: D2.1 (K), D13.1 (K), D28.1 (K), D40.1 (K), J3.9 (MISO), U1.11 ((PDO/PCINT3/MISO)PB3)
/Row2: D4.1 (K), D14.1 (K), D29.1 (K), D41.1 (K), U1.8 ((SS/PCINT0)PB0)
/Row3: D5.1 (K), D15.1 (K), D30.1 (K), D42.1 (K), U1.36 ((ADC7/TDI)PF7)
/Row4: D6.1 (K), D16.1 (K), D31.1 (K), D43.1 (K), U1.37 ((ADC6/TDO)PF6)
/Row5: D7.1 (K), D17.1 (K), D32.1 (K), D44.1 (K), U1.38 ((ADC5/TMS)PF5)
/backlight: Q1.2 (G), U1.30 ((PCINT6/OC1B/OC4B/ADC13)PB6)
/rgb: R25.2, U1.1 ((INT6/AIN0)PE6)
GND: C1.2, C2.1, C3.2, C4.1, C5.2, C6.1, C7.2, C8.2, C9.2, C10.2, C11.2, C12.2, C13.2, C14.2, C15.2, C16.2, D1.3 (VSS), D3.2 (A), D8.2 (A), D9.2 (A), D10.2 (A), D11.2 (A), D12.2 (A), D18.2 (A), D19.2 (A), D20.2 (A), D21.2 (A), D22.2 (A), D23.2 (A), D24.2 (A), D25.2 (A), D26.2 (A), D27.2 (A), D33.2 (A), D34.2 (A), D35.1 (K), D36.2 (A), D37.2 (A), D38.1 (K), D39.2 (A), D45.3 (VSS), D46.3 (VSS), D47.3 (VSS), D48.3 (VSS), D49.3 (VSS), D50.3 (VSS), D51.3 (VSS), D52.3 (VSS), D53.3 (VSS), J1.5 (GND), J1.6 (Shield), J2.5 (GND), J2.6 (Shield), J3.4 (GND), J3.6 (GND), J3.8 (GND), J3.10 (GND), R4.2, SW1.1, U1.5 (UGnd), U1.15 (GND), U1.23 (GND), U1.35 (GND), U1.43 (GND)
unnamed: C1.1, U1.16 (XTAL2), Y1.1
unnamed: C5.1, U1.17 (XTAL1), Y1.2
unnamed: C6.2, U1.6 (Ucap)
unnamed: D1.2 (DOUT), D46.4 (DIN)
unnamed: D1.4 (DIN), R25.1
unnamed: D2.2 (A), SW2.2
unnamed: D3.1 (K), R5.1
unnamed: D4.2 (A), SW3.2
unnamed: D5.2 (A), SW4.2
unnamed: D6.2 (A), SW5.2
unnamed: D7.2 (A), SW6.2, SW7.2
unnamed: D8.1 (K), R6.1
unnamed: D9.1 (K), R7.1
unnamed: D10.1 (K), R8.1
unnamed: D11.1 (K), D12.1 (K), R9.1
unnamed: D13.2 (A), SW8.2
unnamed: D14.2 (A), SW9.2
unnamed: D15.2 (A), SW10.2
unnamed: D16.2 (A), SW11.2
unnamed: D17.2 (A), SW12.2
unnamed: D18.1 (K), R10.1
unnamed: D19.1 (K), R11.1
unnamed: D20.1 (K), R12.1
unnamed: D21.1 (K), R13.1
unnamed: D22.1 (K), R14.1
unnamed: D23.1 (K), R15.1
unnamed: D24.1 (K), R16.1
unnamed: D25.1 (K), R17.1
unnamed: D26.1 (K), R18.1
unnamed: D27.1 (K), R19.1
unnamed: D28.2 (A), SW13.2
unnamed: D29.2 (A), SW14.2
unnamed: D30.2 (A), SW15.2
unnamed: D31.2 (A), SW16.2
unnamed: D32.2 (A), SW17.2
unnamed: D33.1 (K), R20.1
unnamed: D34.1 (K), D35.2 (A), R21.1
unnamed: D36.1 (K), R22.1
unnamed: D37.1 (K), D38.2 (A), R23.1
unnamed: D39.1 (K), R24.1
unnamed: D40.2 (A), SW18.2
unnamed: D41.2 (A), SW20.2
unnamed: D42.2 (A), SW19.1, SW21.2
unnamed: D43.2 (A), SW23.2
unnamed: D44.2 (A), SW22.1, SW24.2
unnamed: D45.4 (DIN), D47.2 (DOUT)
unnamed: D46.2 (DOUT), D48.4 (DIN)
unnamed: D47.4 (DIN), D49.2 (DOUT)
unnamed: D48.2 (DOUT), D50.4 (DIN)
unnamed: D49.4 (DIN), D51.2 (DOUT)
unnamed: D50.2 (DOUT), D52.4 (DIN)
unnamed: D51.4 (DIN), D53.2 (DOUT)
unnamed: D52.2 (DOUT), D53.4 (DIN)
unnamed: J1.2 (D-), J2.2 (D-), R2.2
unnamed: J1.3 (D+), J2.3 (D+), R3.2
unnamed: Q1.3 (S), R5.2, R6.2, R7.2, R8.2, R9.2, R10.2, R11.2, R12.2, R13.2, R14.2, R15.2, R16.2, R17.2, R18.2, R19.2, R20.2, R21.2, R22.2, R23.2, R24.2
unnamed: R2.1, U1.3 (D-)
unnamed: R3.1, U1.4 (D+)
unnamed: R4.1, U1.33 ((~HWB~)PE2)
VCC: C2.2, C3.1, C4.2, C7.1, C8.1, C9.1, C10.1, C11.1, C12.1, C13.1, C14.1, C15.1, C16.1, D1.1 (VDD), D45.1 (VDD), D46.1 (VDD), D47.1 (VDD), D48.1 (VDD), D49.1 (VDD), D50.1 (VDD), D51.1 (VDD), D52.1 (VDD), D53.1 (VDD), J1.1 (VBUS), J2.1 (VBUS), J3.2 (VCC), Q1.1 (D), R1.1, U1.2 (UVcc), U1.7 (VBus), U1.14 (VCC), U1.24 (AVCC), U1.34 (VCC), U1.44 (AVCC)
